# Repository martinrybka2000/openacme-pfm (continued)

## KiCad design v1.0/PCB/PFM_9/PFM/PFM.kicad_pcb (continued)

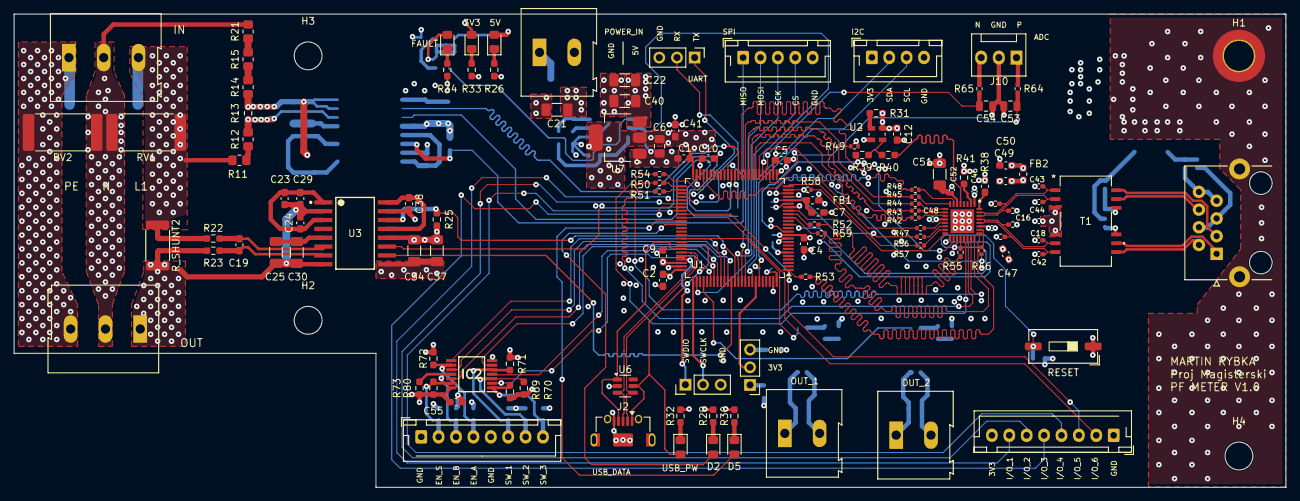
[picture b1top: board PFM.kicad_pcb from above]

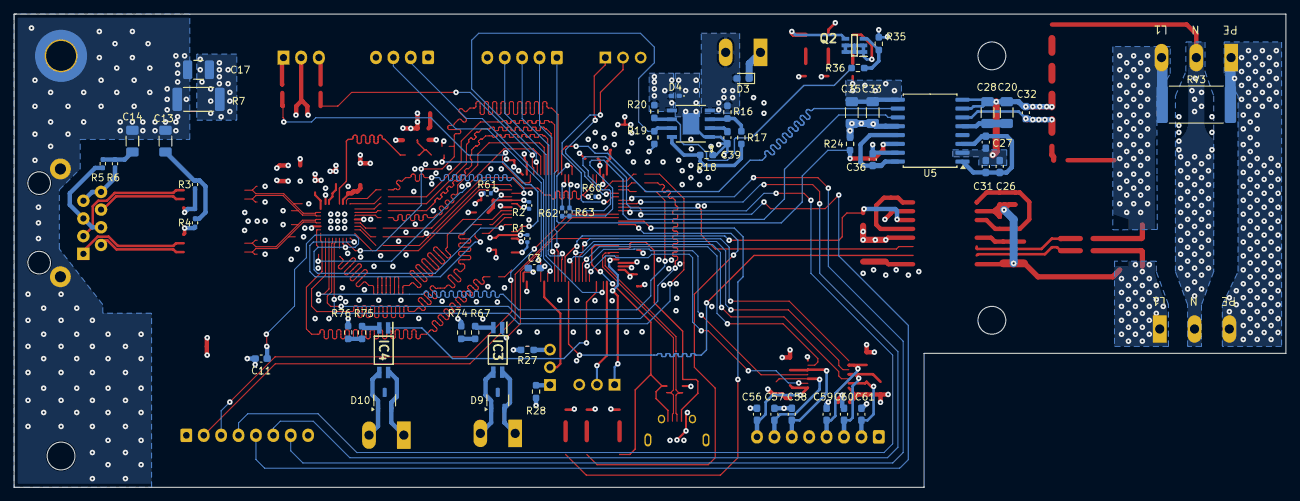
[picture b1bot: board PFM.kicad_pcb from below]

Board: 4 copper layers, 182.8 x 68.0 mm, 183 parts (56 on the bottom side), 155 nets.

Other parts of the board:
RESET: RESET_SW; SW_DIP_SPSTx01_Slide_9.78x4.72mm_W8.61mm_P2.54mm

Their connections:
/STM33/RESET: RESET.2; also elsewhere on the board
GND: RESET.1; also elsewhere on the board

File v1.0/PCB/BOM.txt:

Ref	Qnty	Value	MPN
C1, C2, C3, C4, C5, C7, C9, C10, C11, C12, , C47, C55, C56, C57, C58, C59, C60, C61,	18	100n	On Stan
C24, C27, C36, C38	4	100n	C0603C104K5RACAUTO
C6,	1	4.7u	On Stan
C13, C14,	2	1n, 2KV	8,85342E+11
C16,	1	22n	AC0402KRX7R9BB223
C17,	1	4.7n, 2kV	1210B472K202CT
C18, C42, C43, C44,	4	10p	8,85392E+11
C19,	1	10n	06035C103JAT2A
C20, C25,	2	100n	C3216NP01H104J160AA
C21, C35, C37, C40, C51,	5	1u	12063C105KAT2A
C22,	1	22u	CL31A226MOCLNNC
C23, C26,	2	1u	CGA3E1X7R1E105K080AC
C28, C30, C33, C34,	4	1n	12065C102KAT2A
C29, C31, C32,	3	1n	C0603C102K5RAC7411
C39, C41, C49, C50,	4	2.2u	On Stan
C45, C46, C48,	3	100n	GRM155R61A104KA01J
C52,	1	470p	KGM05ACG1H471JN
C53, C54,	2	5n	08051C502KAT2A
D1,	1	LED_5V	On Stan
D2,	1	LED_RED	On Stan
D3,	1	D_TVS	ESD203B102ELE6327XTMA1
D4,	1	D_TVS	GG040205100N2P
D5,	1	LED_GR	On Stan
D6,	1	LED_USB_PW	On Stan
D7,	1	LED_3V3	On Stan
D8,	1	LED_EFAULT	On Stan
D9, D10,	2	ESDA5V3L	771-PESD36VS2UT215
FB1, FB2,	2	1000Ohm	On Stan
IC1,	1	LAN8740AI-EN-TR	579-LAN8740AI-EN-TR
IC2,	1	SN74LVC14APWRG3	595-SN74LVC14APWRG3
IC3, IC4,	2	PS2802-1-F3-A	On Stan
J1,	1	Boot	On Stan
J2,	1	USB_OTG	538-47590-0001
J3,	1	GRID_term	710-691502710003
J4,	1	5V_term	On Stan
J5,	1	OUT_term	710-691502710003
J6,	1	PROG_DEBUG	On Stan
J7,	1	RJHSE-5380	On Stan
J8,	1	UART_DEBUG	On Stan
J9,	1	OLED_I2C	On Stan
J10,	1	ADC_EXT_CONN	TBC05-03-1-G-G
J11,	1	SPI_EXT	On Stan
J12,	1	OUT_1	On Stan
J13,	1	OUT_2	On Stan
J15,	1	Free_pins	On Stan
J17,	1	Butts_conn	On Stan
Q2,	1	SI3493DDV-T1-GE3	On Stan
R3, R4, R5, R6,	4	75	ERA-2AEB750X
R7,	1	1M	RC2512JK-071ML
R8, R9, R10, R37, R64, R65,	6	49.9	On Stan
R11, R12, R14, R15, R21,	5	715k	667-ERA-6AEB7153V
R13,	1	10k, 0.1%	667-ERA-3AEB103V
R16, R17,	2	94,2	RN73H1JTTD94R2F50
R18, R24, R25, R35,	4	47k	On Stan
R19, R36,	2	1k	On Stan
R20, R27, R28, R31, R41, R69, R70, R71, R72, R73, R80,	11	10k	On Stan
R22, R23,	2	10	RCA060310R0FKEAHP
R26, R29, R30, R32, R33, R34,	6	680	On Stan
R38,	1	12.1k	RT0603FRE0712K1L
R39, R40,	2	33	On Stan
R42, R43, R44, R45, R46, R47, R48, R56, R57, R58, R59,	11	56	RT0402DRE0756RL
R49, R61,	2	1.5k	MCS04020C1501FE000
R50, R51, R52, R53, R54, R55,	6	100	RR0510P-101-D
R60,	1	4.7k	MCS04020C4701FE000
R67, R74, R75, R76,	4	150	On Stan
R_SHUNT2,	1	25m	279-TLRP3A30DR025FTE
RESET1,	1	RESET_SW	On Stan
RV1, RV2, RV3,	3	Varistor	MOVS4032V230
T1,	1	ALANL100X1-DE12DT	815-ALANL100X1DE12DT
U1,	1	STM32H750VBTx	STM32H750VBT6
U2,	1	DSC1001DI1-025.0000	998-1001DI1-025.0000
U3,	1	AMC3306M25DWE	AMC3306M25DWER
U4,	1	TPS259620DDAR	595-TPS259620DDAR
U5,	1	AMC3336	AMC3336DWER
U6,	1	USBLC6-4SC6	511-USBLC6-4SC6Y
U7,	1	TLV1117-33	595-TLV1117LV33DCYR

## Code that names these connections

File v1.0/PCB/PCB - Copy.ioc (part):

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Mcu.Name=STM32H750VBTx
Mcu.Package=LQFP100
Mcu.UserName=STM32H750VBTx
PA0.Mode=MII
PA0.Signal=ETH_CRS
PA1.Mode=MII
PA1.Signal=ETH_RX_CLK
PA10.Mode=OTG/Dual_Role_Device
PA10.Signal=USB_OTG_FS_ID
PA11.Mode=OTG/Dual_Role_Device
PA11.Signal=USB_OTG_FS_DM
PA12.Mode=OTG/Dual_Role_Device
PA12.Signal=USB_OTG_FS_DP
PA13\ (JTMS/SWDIO).Mode=Serial_Wire
PA13\ (JTMS/SWDIO).Signal=DEBUG_JTMS-SWDIO
PA14\ (JTCK/SWCLK).Mode=Serial_Wire
PA14\ (JTCK/SWCLK).Signal=DEBUG_JTCK-SWCLK
PA15\ (JTDI).Mode=NSS_Signal_Hard_Output
PA15\ (JTDI).Signal=SPI1_NSS
PA2.Mode=MII
PA2.Signal=ETH_MDIO
PA3.Mode=MII
PA3.Signal=ETH_COL
PA4.Signal=ADCx_INP18
PA5.Signal=ADCx_INN18
PA6.GPIOParameters=GPIO_Label
PA6.GPIO_Label=TPS_I_MON
PA6.Signal=ADCx_INP3
PA7.Mode=MII
PA7.Signal=ETH_RX_DV
PA9.Mode=Activate_VBUS
PA9.Signal=USB_OTG_FS_VBUS
PB0.Mode=MII
PB0.Signal=ETH_RXD2
PB1.Mode=MII
PB1.Signal=ETH_RXD3
PB10.Mode=Activate Rx Err signal
PB10.Signal=ETH_RX_ER
PB11.Mode=MII
PB11.Signal=ETH_TX_EN
PB12.Mode=MII
PB12.Signal=ETH_TXD0
PB13.Mode=MII
PB13.Signal=ETH_TXD1
PB14.Mode=Asynchronous
PB14.Signal=USART1_TX
PB15.Mode=Asynchronous
PB15.Signal=USART1_RX
PB2.Mode=Activate Tx Err signal
PB2.Signal=ETH_TX_ER
PB3\ (JTDO/TRACESWO).Mode=Full_Duplex_Master
PB3\ (JTDO/TRACESWO).Signal=SPI1_SCK
PB4\ (NJTRST).Mode=Full_Duplex_Master
PB4\ (NJTRST).Signal=SPI1_MISO
PB5.Mode=Full_Duplex_Master
PB5.Signal=SPI1_MOSI
PB6.GPIOParameters=GPIO_Pu
PB6.GPIO_Pu=GPIO_PULLUP
PB6.Mode=I2C
PB6.Signal=I2C1_SCL
PB7.GPIOParameters=GPIO_Pu
PB7.GPIO_Pu=GPIO_PULLUP
PB7.Mode=I2C
PB7.Signal=I2C1_SDA
PC1.Mode=MII
PC1.Signal=ETH_MDC
PC11.GPIOParameters=GPIO_Label
PC11.GPIO_Label=OUT_2
PC11.Signal=GPIO_Output
PC2_C.Mode=MII
PC2_C.Signal=ETH_TXD2
PC3_C.Mode=MII
PC3_C.Signal=ETH_TX_CLK
PC4.Mode=MII
PC4.Signal=ETH_RXD0
PC5.Mode=MII
PC5.Signal=ETH_RXD1
PC9.GPIOParameters=GPIO_Label
PC9.GPIO_Label=OUT_1
PC9.Signal=GPIO_Output
PD0.GPIOParameters=GPIO_Label
PD0.GPIO_Label=Butt_1
PD0.Signal=GPIO_Input
PD1.GPIOParameters=GPIO_Label
PD1.GPIO_Label=Butt_2
PD1.Signal=GPIO_Input
PD14.GPIOParameters=GPIO_Label
PD14.GPIO_Label=LED_GREEN
PD14.Signal=GPIO_Output
PD15.GPIOParameters=GPIO_Label
PD15.GPIO_Label=LED_RED
PD15.Signal=GPIO_Output
PD2.GPIOParameters=GPIO_Label
PD2.GPIO_Label=Butt_3
PD2.Signal=GPIO_Input
PD3.GPIOParameters=GPIO_Label
PD3.GPIO_Label=ENC_A
PD3.Signal=GPIO_Input
PD4.GPIOParameters=GPIO_Label
PD4.GPIO_Label=ENC_B
PD4.Signal=GPIO_Input
PD5.GPIOParameters=GPIO_Label
PD5.GPIO_Label=ENC_Butt
PD5.Signal=GPIO_Input
PD6.Signal=S_DATAIN1DFSDM1
PD7.GPIOParameters=GPIO_PuPd,GPIO_Label
PD7.GPIO_Label=ADC_I_DIAG
PD7.GPIO_PuPd=GPIO_PULLUP
PD7.Signal=GPIO_Input
PE10.GPIOParameters=GPIO_PuPd,GPIO_Label
PE10.GPIO_Label=ADC_V_DIAG
PE10.GPIO_PuPd=GPIO_PULLUP
PE10.Signal=GPIO_Input
PE2.Mode=MII
PE2.Signal=ETH_TXD3
PE7.Signal=S_DATAIN2DFSDM1
PE8.GPIOParameters=GPIO_Label
PE8.GPIO_Label=DFSDM_U_CLKOUT2
PE8.Signal=GPIO_Output
PE9.Signal=S_CKOUTDFSDM1
PH0-OSC_IN\ (PH0).Mode=HSE-External-Oscillator
PH0-OSC_IN\ (PH0).Signal=RCC_OSC_IN
PH1-OSC_OUT\ (PH1).Mode=HSE-External-Oscillator
PH1-OSC_OUT\ (PH1).Signal=RCC_OSC_OUT
RCC.HSE_VALUE=25000000
RCC.SYSCLKFreq_VALUE=75000000
RCC.SYSCLKSource=RCC_SYSCLKSOURCE_PLLCLK
board=custom
